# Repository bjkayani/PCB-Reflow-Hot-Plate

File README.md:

# PCB Reflow Hot Plate

The PCB Reflow Hot Plate is a temperature controlled 120 x 70 mm hot plate designed to reflow solder SMD circuit boards. This project was started due to a gap in the commercial solutions for a mid sized form factor hot plate. 

This project is a work in progress and various elements of it are continually improving and changing. Refer to the build guide for more information including a compatibility table. 

<br>

</a>

<br>

## Features

- 120x70mm (4.7x2.7in) aluminum hot plate
- 300 Watt PTC heating element
- ESP32-C3 based control board
- Tuned PID controller with configurable parameters
- Reflow mode with customizable reflow profiles
- Constant temeprature (heat) mode
- Upto 260 C temperature allows lead free reflow
- Easy to use GUI using 0.96" OLED display and 3 buttons
- Serial debugging over USB to monitor temperature
- Single power cable required for operation

<br>

## Design

### The main design considerations were:
- Atleast 70x70mm reflow area (the Miniware is 30x30mm)
- Slim design to allow tweezer manipulation with hands resting on the desk
- Commercially viable solution with a long operating life
- Easy to operature and minimal setup process
- Safe operation with multiple layers of safety

With these considerations in mind, this is the design I came up with. It uses an off the shelf heating plate with an embedded 300W heating element. I designed my own control board that includes everything needed to control the heating plate and can run entirely from mains input. 

I went with a small 0.96" OLED display and three buttons as that seems adequate to control the UI. The UI is simple and intuitive yet provides all the functionality needed to operate and customize the hot plate. 

Its all packaged in a slim, rectangular 3D printed case that exposes the hot plate provide a window for the display and integrated buttons. The hotplate has insulation placed underneath it to prevent heat loss from the bottom. The case needs to be printed in a relatively temperature resistant material to avoid warping at high temperature. 

</a>

<br>

## PCB

The PCB is designed in KiCAD. Its a 2-layer design and it contains everything needed to run the hot plate with a single mains input. The USB-C port provides power to the DC section and allows for programming the ESP32-C3 microcontroller. The OLED display is on a separate daughter board and mounted using M2 standoffs. A standard 0.96" OLED display module should work although there is some variation in the models avaiable. More information regarding that coming soon. 

### Version 1.1:

- [BOM](PCB/pcb-reflow-hot-plate/bom/pcb-reflow-hot-plate_1.2.html)
- [Gerber](PCB/pcb-reflow-hot-plate/output/pcb-reflow-hot-plate_Rev1.2.zip)

### Revision History

- Rev 1.0
    - Initial design
- Rev 1.1
    - AC-DC converter changed to HLK-5M05
    - SSR changed to popular OMRON compatible footprint
    - OLED display module moved to center align with buttons
    - SSR supply changed to +5V
    - AC in connector mounting peg holes increased in size
    - Minor silk screen updates
- Rev 1.2
    - AC in connector mounting holes further widened
    - OLED module footprint changed for newer modules
    - Tactile switches changed to 4.5x4.5x5mm
    - Neopixel added
    - Stemma QT connector added
    - SMD buzzer changed to SMD
    - AC fuse added
- Rev 1.3
    - RGB LED moved down
    - Heater and thermocouple connector rotated
    - Thermocouple GND line grounded

</a>
</a>

<br>

## Code

The code is written in Arduino IDE due to its ease of use and simlicity over PlatformIO and native ESP SDK. The code is split up into multiple files with each file containing functions relating to specific funcionality. 

The code is continually under development and I am adding new features regularly. I have also commented the code so that its easy to understand. Feel free to look through the code, file an issue if you encounter one or request features to be added. 

I have a lot of features I want to add that are on the road map but I first wanted to get the basic funtionality working and tested. These are listed at the start of the [main program file](Code/pcb-reflow-hot-plate/pcb-reflow-hot-plate.ino). 

<br>

## CAD

The housing is designed in SolidWorks. Its designed as a two part enclosure with a tab and screws to hold the two together. The heating plate comes with silicon feet that fit into the base. The base is raised to be slighly protruding from the top surface and insulation is put underneath to avoid heat dissipation from the bottom. 

The latest STL and design files can be found in the CAD folder. The assembly is missing the PCB due to import issues from KiCAD into SolidWorks.

</a>
</a>

<br>

## Build Guide

### Build guide is coming soon ...

### Compatibility Table

| PCB (HW) | OLED Module | Code (FW) | CAD |
| :---: | :---------: | :---: | :---: |
| Rev 1.0 | SSD1306 0.96" 25.2x26mm <br> [AliExpress Link](https://www.aliexpress.us/item/2251832644208699.html?spm=a2g0o.order_list.order_list_main.11.21ef1802tOmkk3&gatewayAdapt=glo2usa4itemAdapt&_randl_shipto=US#nav-specification) | 1.0 | Housing Top v1 <br> Housing Base v1 |
| Rev 1.1 |  SSD1306 0.96" 27.6x27.6mm <br> [Amazon Link](https://amzn.to/43KL0ey) | 1.0  | Housing Top v2 <br> Housing Base v1 |
| Rev 1.2 |  SSD1306 0.96" 27.6x27.6mm <br> [Amazon Link](https://amzn.to/43KL0ey) | 1.1 |Housing Top v3 <br> Housing Base v2 <br> Light Pipe v1 |
| Rev 1.3 |  SSD1306 0.96" 27.6x27.6mm <br> [Amazon Link](https://amzn.to/43KL0ey) | 1.1 | Housing Top v3 <br> Housing Base v2 <br> Light Pipe v2 |

<br>

## Future Ideas
- [ ] Add mounting holes and pogo pin body connectors for accessories such as cooling fan, external temperature probe, fume extractor
- [ ] Make display separate from main PCB and shrink the main PCB
- [ ] Move the buttons to the bottom of the display
- [ ] Increase the size of the display to ~1.5in
- [ ] Switch to DC heater with thinner hot plate and USB-C PD (100 Watts)
- [ ] Switch to a square heating element
- [ ] Add integrated active cooling that blows air parallel to the hot plate
- [ ] Add multiple sensing options (thermocouple, thermistor etc.)
- [x] Add AC protection fuse
- [ ] Protection for reverse wired thermocouple

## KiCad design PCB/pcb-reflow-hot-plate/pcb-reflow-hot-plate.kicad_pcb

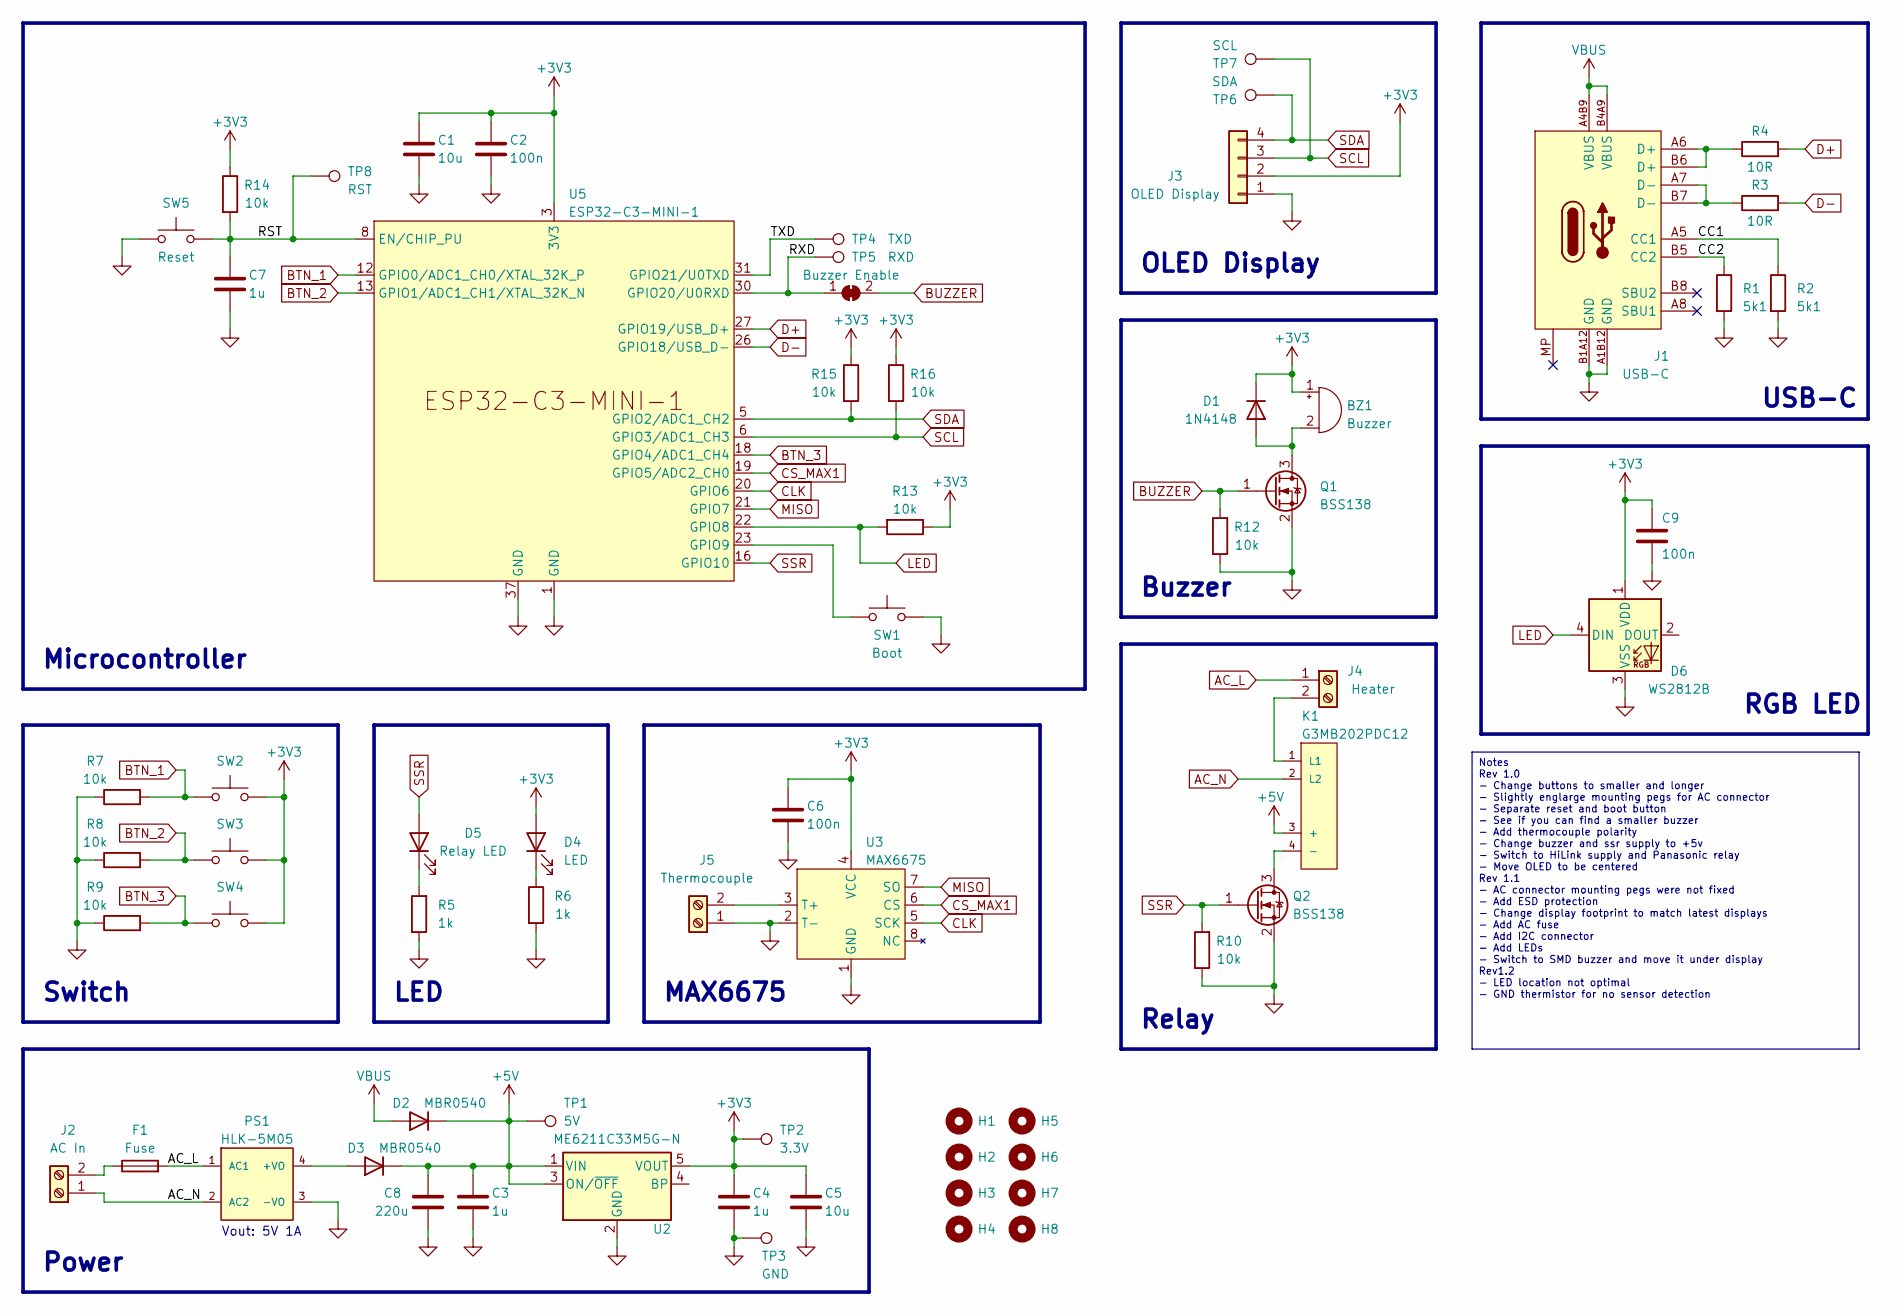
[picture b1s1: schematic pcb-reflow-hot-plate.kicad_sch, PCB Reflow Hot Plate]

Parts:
BZ1: Buzzer; CMI-9653S-SMT-TR; Part Number HNB09A03; LCSC Part Number C96102
C1, C5: 10u; C_0603_1608Metric; Part Number GRM188B30J106ME47D; LCSC Part Number C15499
C2, C6, C9: 100n; C_0402_1005Metric; Part Number GCM155R71C104KA40D; LCSC Part Number C126523
C3, C4, C7: 1u; C_0402_1005Metric; Part Number GRM155R61C105KE01D; LCSC Part Number C77007
C8: 220u; C_Elec_6.3x5.8; Part Number RST220UF10V018; LCSC Part Number C4747973
D1: 1N4148; D_SOD-123; Part Number 1N4148W-7-F; LCSC Part Number C83528
D2, D3: MBR0540; D_SOD-123; Part Number MBR0540; LCSC Part Number C77337
D4: LED; LED_0603_1608Metric; Part Number NCD0603G1; LCSC Part Number C84267
D5: Relay LED; LED_0603_1608Metric; Part Number NCD0603G1; LCSC Part Number C84267
D6: WS2812B; LED_WS2812B_PLCC4_5.0x5.0mm_P3.2mm; Part Number WS2812B-B/W; LCSC Part Number C114586
F1: Fuse; Fuse_Littelfuse_395Series; Part Number SQT3.15M; LCSC Part Number C312031
H1, H2, H3, H4: MountingHole; MountingHole_3.2mm_M3_Pad_Via
H5, H6, H7, H8: MountingHole; MountingHole_2.2mm_M2_Pad
J1: USB-C; Conn_USB-C_Receptacle_16Pin_Horizontal; Part Number TYPE-C 16PIN 2MD(073); LCSC Part Number C2765186
J2: AC In; Conn_IEC-C1_AC_Receptacle_2-Pin; Part Number RT-C08-F2-WH; LCSC Part Number C309250
J3: OLED Display; PinHeader_1x04_P2.54mm_Vertical; Part Number 2685Y-104CNG1SNA01; LCSC Part Number C350310
J4: Heater; TerminalBlock_RND_205-00001_1x02_P5.00mm_Horizontal; Part Number DB128V-5.0-2P-GN-S; LCSC Part Number C395860
J5: Thermocouple; TerminalBlock_4Ucon_1x02_P3.50mm_Horizontal; Part Number DB301V-3.5-2P-GN-S; LCSC Part Number C695629
JP1: Buzzer Enable; SolderJumper-2_P1.3mm_Bridged_RoundedPad1.0x1.5mm
K1: G3MB202PDC12; RELAY_G3MB202PDC12; Part Number AQG22205; LCSC Part Number C124000
PS1: HLK-5M05; CONV_HLK-5M05; Part Number HLK-5M05; LCSC Part Number C209907
Q1, Q2: BSS138; SOT-23; Part Number BSS138; LCSC Part Number C2874697
R1, R2: 5k1; R_0402_1005Metric; Part Number RC0402FR-075K1L; LCSC Part Number C105872
R3, R4: 10R; R_0402_1005Metric; Part Number RC0402FR-0710RL; LCSC Part Number C138066
R5, R6: 1k; R_0402_1005Metric; Part Number RC0603FR-071KL; LCSC Part Number C22548
R7, R8, R9, R10, R12, R13, R14, R15, R16: 10k; R_0402_1005Metric; Part Number RC0603FR-0710KL; LCSC Part Number C98220
SW1: Boot; GT-TC034F-H018-L1; Part Number GT-TC034F-H018-L1; LCSC Part Number C2835023
SW2, SW3, SW4: TL3305AF260QG; Part Number GT-TC074B-H050-L1; LCSC Part Number C843607
SW5: Reset; GT-TC034F-H018-L1; Part Number GT-TC034F-H018-L1; LCSC Part Number C2835023
TP1: 5V; TestPoint_Pad_D1.5mm
TP2: 3.3V; TestPoint_Pad_D1.5mm
TP3: GND; TestPoint_Pad_D1.5mm
TP4: TXD; TestPoint_Pad_D1.5mm
TP5: RXD; TestPoint_Pad_D1.5mm
TP6: SDA; TestPoint_Pad_D1.5mm
TP7: SCL; TestPoint_Pad_D1.5mm
TP8: RST; TestPoint_Pad_D1.5mm
U2: ME6211C33M5G-N; SOT-23-5; Part Number ME6211C33M5G-N; LCSC Part Number C82942
U3: MAX6675; SOIC-8_3.9x4.9mm_P1.27mm; Part Number MAX6675ISA+T; LCSC Part Number C16030
U5: ESP32-C3-MINI-1; Part Number ESP32-C3-MINI-1-N4; LCSC Part Number C5290152

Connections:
+3V3: BZ1.1 (-), C1.1, C2.1, C4.1, C5.1, C6.1, C9.1, D1.1 (K), D4.2 (A), D6.1 (VDD), J3.2, R13.1, R14.1, R15.1, R16.1, SW2.2, SW3.2, SW4.2, TP2.1, U2.5 (VOUT), U3.4 (VCC), U5.3 (3V3)
+5V: C3.1, C8.1, D2.1 (K), D3.1 (K), K1.3 (+), TP1.1, U2.1 (VIN), U2.3 (ON/~OFF)
/CC1: J1.A5 (CC1), R2.1
/CC2: J1.B5 (CC2), R1.1
/RST: C7.1, R14.2, SW5.2, TP8.1, U5.8 (EN/CHIP_PU)
/RXD: JP1.1 (A), TP5.1, U5.30 (GPIO20/U0RXD)
/TXD: TP4.1, U5.31 (GPIO21/U0TXD)
AC_L: F1.2, J4.1, PS1.1 (AC1)
AC_N: J2.1, K1.2 (L2), PS1.2 (AC2)
BTN_1: R7.2, SW2.1, U5.12 (GPIO0/ADC1_CH0/XTAL_32K_P)
BTN_2: R8.2, SW3.1, U5.13 (GPIO1/ADC1_CH1/XTAL_32K_N)
BTN_3: R9.2, SW4.1, U5.18 (GPIO4/ADC1_CH4)
BUZZER: JP1.2 (B), Q1.1 (G), R12.2
CLK: U3.5 (SCK), U5.20 (GPIO6)
CS_MAX1: U3.6 (CS), U5.19 (GPIO5/ADC2_CH0)
D+: R4.2, U5.27 (GPIO19/USB_D+)
D-: R3.2, U5.26 (GPIO18/USB_D-)
GND: C1.2, C2.2, C3.2, C4.2, C5.2, C6.2, C7.2, C8.2, C9.2, D6.3 (VSS), J1.A1B12 (GND), J1.B1A12 (GND), J3.1, J5.1, PS1.3 (-VO), Q1.2 (S), Q2.2 (S), R1.2, R2.2, R5.1, R6.2, R7.1, R8.1, R9.1, R10.1, R12.1, SW1.2, SW5.1, TP3.1, U2.2 (GND), U3.1 (GND), U3.2 (T-), U5.1 (GND), U5.2 (GND), U5.11 (GND), U5.14 (GND), U5.36 (GND), U5.37 (GND), U5.38 (GND), U5.39 (GND), U5.40 (GND), U5.41 (GND), U5.42 (GND), U5.43 (GND), U5.44 (GND), U5.45 (GND), U5.46 (GND), U5.47 (GND), U5.48 (GND), U5.49 (GND), U5.50 (GND), U5.51 (GND), U5.52 (GND), U5.53 (GND)
LED: D6.4 (DIN), R13.2, U5.22 (GPIO8)
MISO: U3.7 (SO), U5.21 (GPIO7)
unnamed: BZ1.2 (+), D1.2 (A), Q1.3 (D)
unnamed: D3.2 (A), PS1.4 (+VO)
unnamed: D4.1 (K), R6.1
unnamed: D5.1 (K), R5.2
unnamed: J1.A6 (D+), J1.B6 (D+), R4.1
unnamed: J1.A7 (D-), J1.B7 (D-), R3.1
unnamed: F1.1, J2.2
unnamed: J4.2, K1.1 (L1)
unnamed: J5.2, U3.3 (T+)
unnamed: K1.4 (-), Q2.3 (D)
unnamed: SW1.1, U5.23 (GPIO9)
SCL: J3.3, R16.2, TP7.1, U5.6 (GPIO3/ADC1_CH3)
SDA: J3.4, R15.2, TP6.1, U5.5 (GPIO2/ADC1_CH2)
SSR: D5.2 (A), Q2.1 (G), R10.2, U5.16 (GPIO10)
VBUS: D2.2 (A), J1.A4B9 (VBUS), J1.B4A9 (VBUS)

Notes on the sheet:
Notes Rev 1.0 - Change buttons to smaller and longer - Slightly englarge mounting pegs for AC connector - Separate reset and boot button - See if you can find a smaller buzzer - Add thermocouple polarity - Change buzzer and ssr supply to +5v - Switch to HiLink supply and Panasonic relay - Move OLED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
LED
USB-C
RGB LED
Power
Relay
Switch
MAX6675
Vout: 5V 1A
Microcontroller
Buzzer
OLED Display

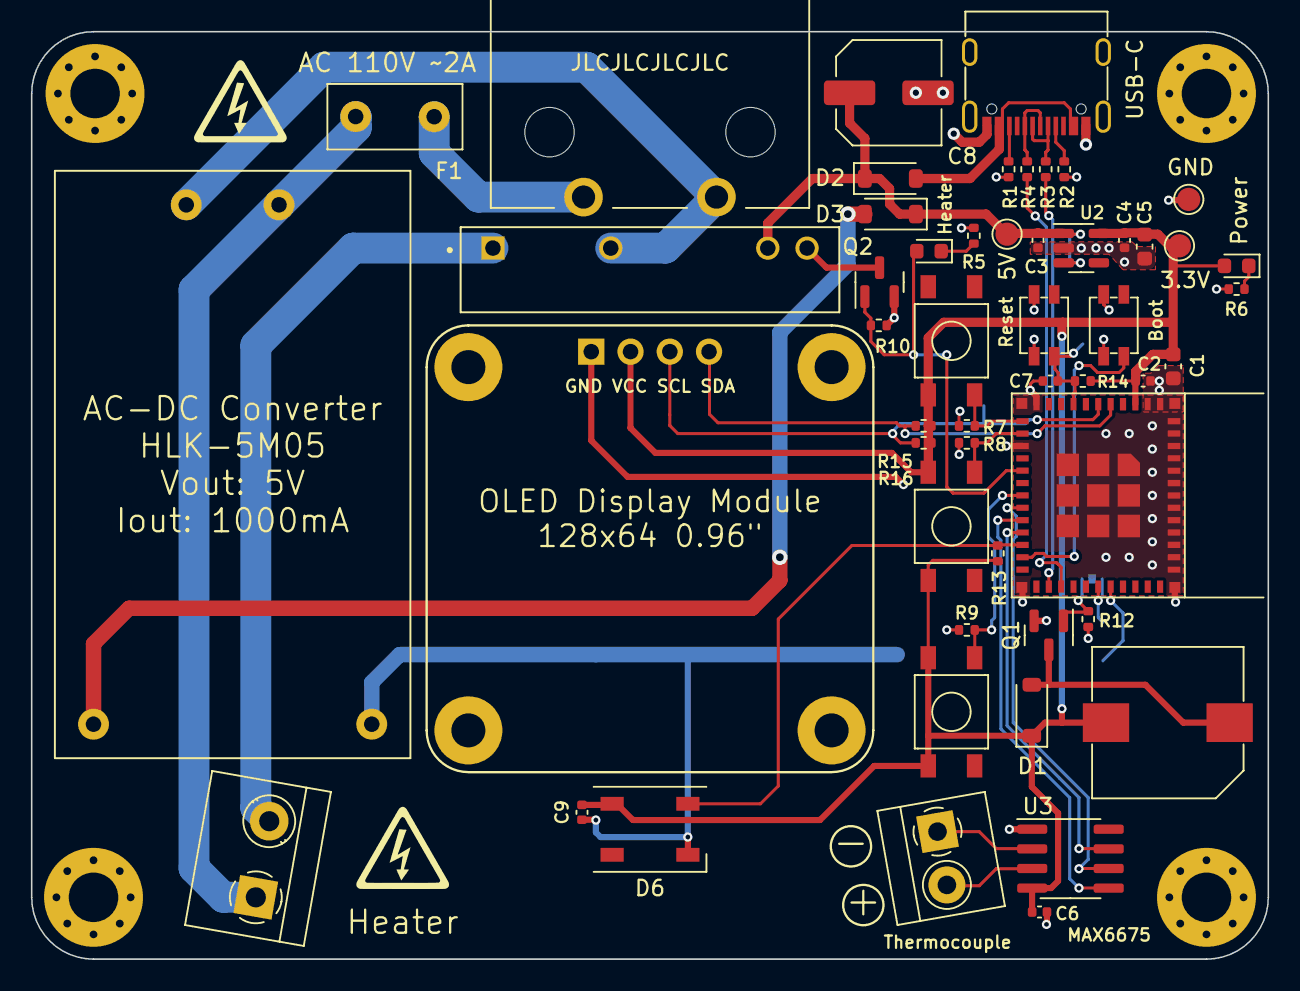
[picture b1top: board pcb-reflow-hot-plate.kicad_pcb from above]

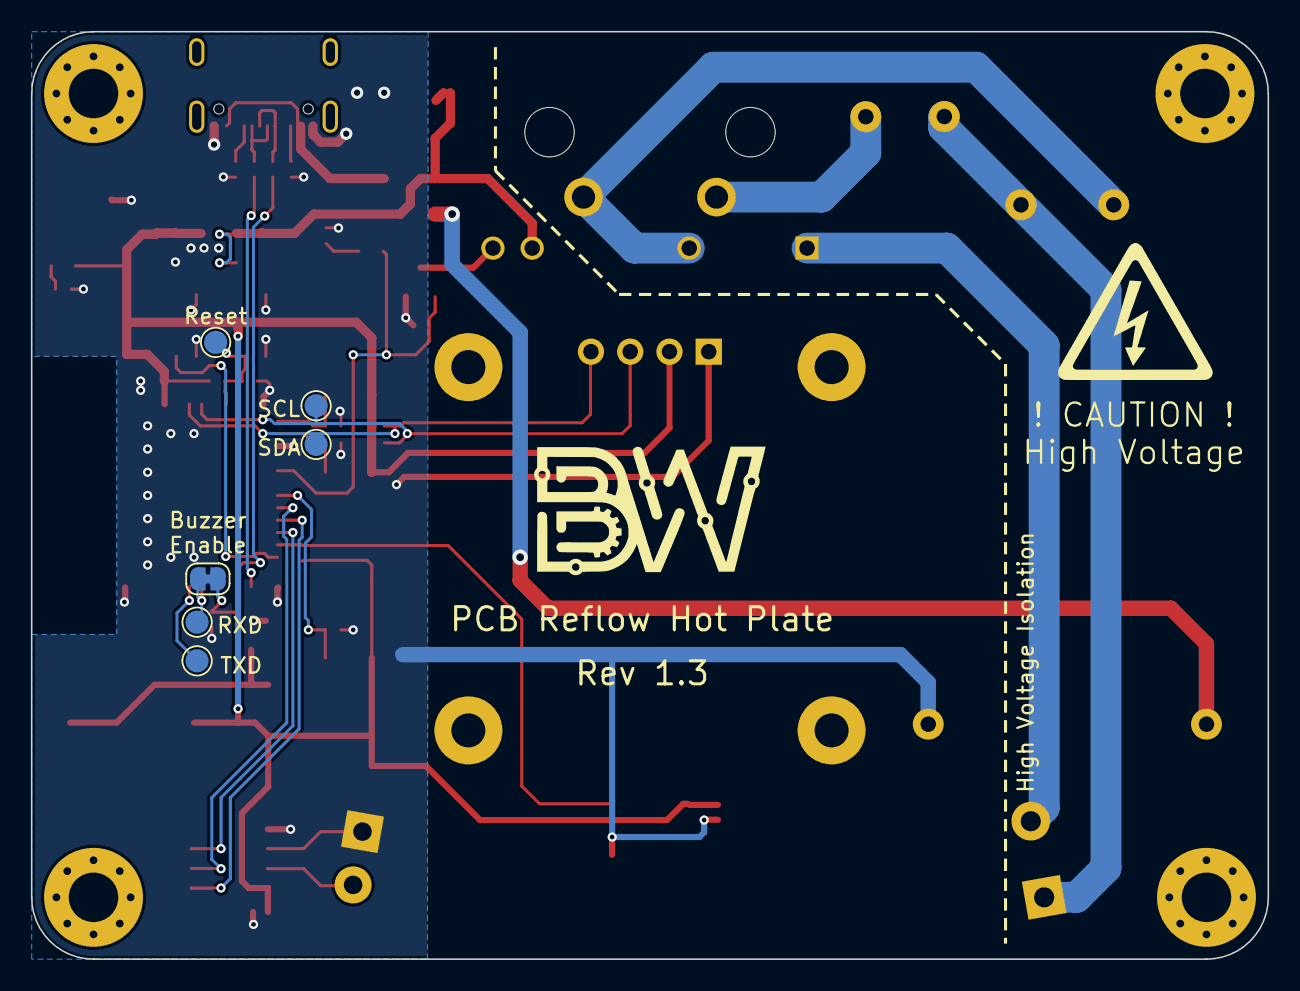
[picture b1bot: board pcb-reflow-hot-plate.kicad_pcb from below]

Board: 2 copper layers, 80.0 x 60.0 mm, 66 parts (6 on the bottom side), 35 nets.

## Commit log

2023-04-12 initial commit (code, cad)
2023-04-14 Rev 1.1 PCB, housing update
2023-04-14 more test data, logger code, reorg
2023-04-16 cad update, readme update
2023-04-16 more test data, readme updated
2023-04-18 buzzer sequence added, readme updated
2023-04-20 safety features, bug fix, housing update
2023-04-26 housing design update
2023-04-27 PCB Rev 1.2
2023-05-04 HW 1.0 lock
2023-06-02 new cad
2023-06-02 restore stash with led start
2023-06-02 CAD cleanup
2023-06-02 rev 1.0 code integrated
2023-09-24 rgb status led added
2023-09-24 cad cleanup and update
2023-09-24 pcb rev 1.3
2023-09-24 readme update, git-ignore update
2024-01-04 semi working web portal
2024-01-04 housing top cad update

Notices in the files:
parts and their libraries:
Copyright 2021 Accelerated Designs. All rights reserved.
